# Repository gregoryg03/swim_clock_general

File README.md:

# swim_clock_general
General Project code development and other related files

Basic testing is being conducted on Arduino Uno with 4 7-segment LEDs

Plan to move to ESP 32

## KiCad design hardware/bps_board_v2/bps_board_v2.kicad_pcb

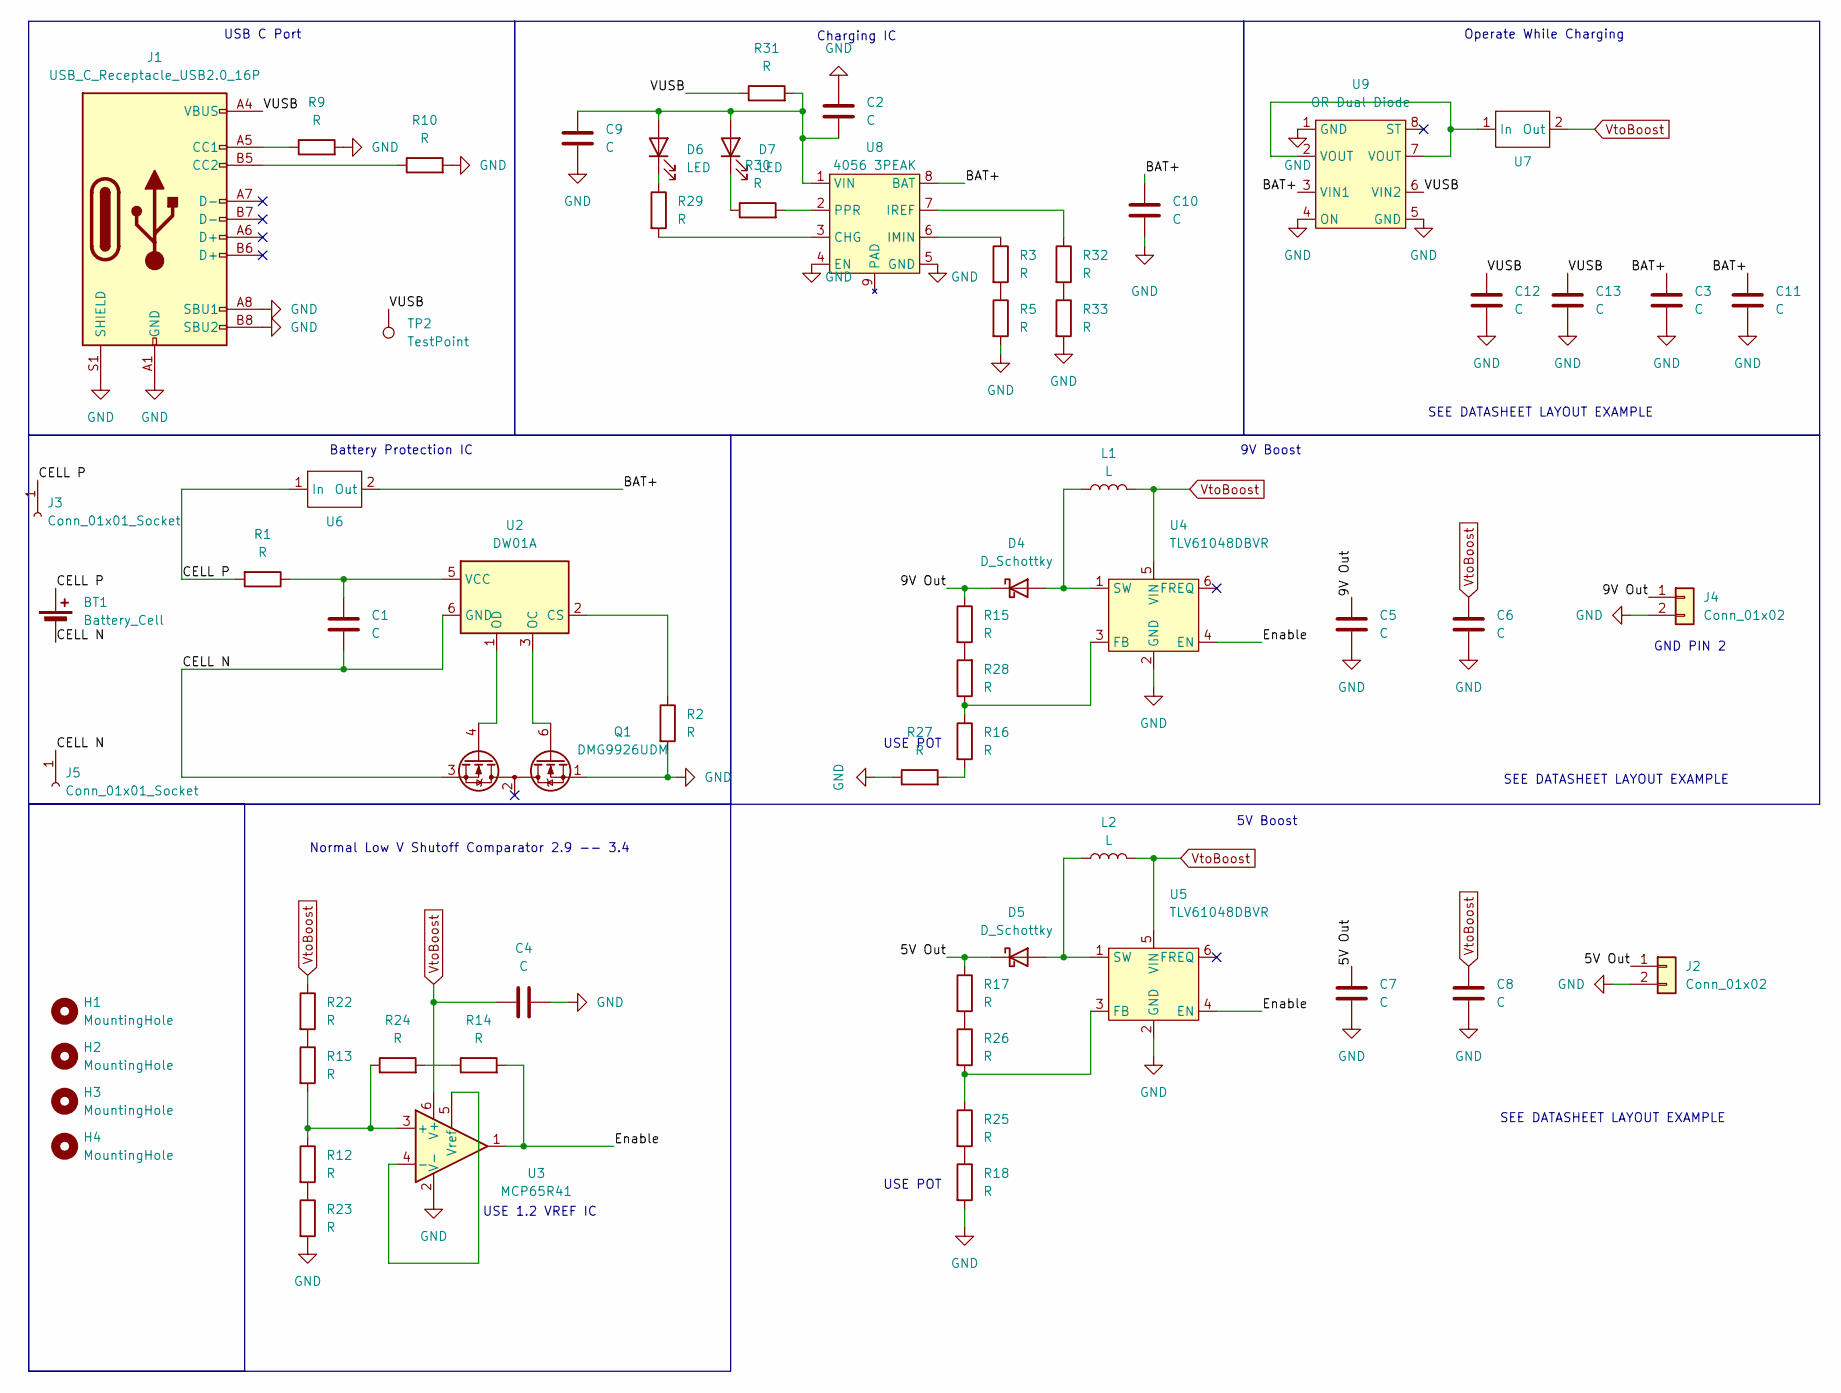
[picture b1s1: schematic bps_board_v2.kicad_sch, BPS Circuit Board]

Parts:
BT1: Battery_Cell; 18650 8mm Strip
C1, C2, C3, C4, C5, C6, C7, C8, C9, C10, C11, C12, C13: C; C_1206_3216Metric_Pad1.33x1.80mm_HandSolder
D4, D5: D_Schottky; MBRS130LT3G Diode
D6, D7: LED; LED_0603_1608Metric_Pad1.05x0.95mm_HandSolder
H1, H2, H3, H4: MountingHole; MountingHole_3.2mm_M3
J1: USB_C_Receptacle_USB2.0_16P; USB_C_Receptacle_GCT_USB4085
J2, J4: Conn_01x02; JST_EH_B2B-EH-A_1x02_P2.50mm_Vertical
J3, J5: Conn_01x01_Socket; EmptyPad
L1, L2: L; InductorFixed
Q1: DMG9926UDM; SOT-23-6
R1, R2, R3, R5, R9, R10, R12, R13, R14, R15, R16, R17, R18, R22, R23, R24, R25, R26, R27, R28, R29, R30, R31, R32, R33: R; R_1206_3216Metric_Pad1.30x1.75mm_HandSolder
TP2: TestPoint; TestPoint_THTPad_2.5x2.5mm_Drill1.2mm
U2: DW01A; SOT-23-6
U3: MCP65R41; SOT-23-6
U4, U5: TLV61048DBVR; SOT-23-6_Handsoldering
U6, U7: 22AWG Wire Jump
U8: 4056 3PEAK; SOIC-8-1EP_3.9x4.9mm_P1.27mm_EP2.41x3.3mm_ThermalVias
U9: OR Dual Diode; SOT-583-8

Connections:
/5V Out: C7.1, D5.1 (K), J2.1, R17.1
/9V Out: C5.1, D4.1 (K), J4.1, R15.1
/BAT+: C3.1, C10.1, C11.1, U6.2 (Out), U8.8 (BAT), U9.3 (VIN1)
/CELL N: BT1.2 (-), C1.2, J5.1, Q1.3 (S2), U2.6 (GND)
/CELL P: BT1.1 (+), J3.1, R1.2, U6.1 (In)
/Enable: R14.2, U3.1, U4.4 (EN), U5.4 (EN)
/VUSB: C12.1, C13.1, J1.A4 (VBUS), J1.A9 (VBUS), J1.B4 (VBUS), J1.B9 (VBUS), R31.1, TP2.1, U9.6 (VIN2)
GND: C2.1, C3.2, C4.2, C5.2, C6.2, C7.2, C8.2, C9.2, C10.2, C11.2, C12.2, C13.2, J1.A1 (GND), J1.A8 (SBU1), J1.A12 (GND), J1.B1 (GND), J1.B8 (SBU2), J1.B12 (GND), J1.S1 (SHIELD), J2.2, J4.2, Q1.1 (D1), R2.2, R5.2, R9.2, R10.2, R18.2, R23.2, R27.1, R33.2, U3.2 (V-), U4.2 (GND), U5.2 (GND), U8.4 (EN), U8.5 (GND), U9.1 (GND), U9.4 (ON), U9.5 (GND)
unnamed: D4.2 (A), L1.1, U4.1 (SW)
unnamed: D5.2 (A), L2.1, U5.1 (SW)
unnamed: C2.2, C9.1, D6.2 (A), D7.2 (A), R31.2, U8.1 (VIN)
unnamed: D6.1 (K), R29.1
unnamed: D7.1 (K), R30.1
unnamed: J1.A5 (CC1), R9.1
unnamed: J1.B5 (CC2), R10.1
unnamed: Q1.6 (G1), U2.3 (OC)
unnamed: Q1.4 (G2), U2.1 (OD)
unnamed: R3.2, R5.1
unnamed: R12.2, R23.1
unnamed: R13.1, R22.2
unnamed: R14.1, R24.2
unnamed: R15.2, R28.2
unnamed: R16.2, R27.2
unnamed: R17.2, R26.1
unnamed: R18.1, R25.2
unnamed: R32.2, R33.1
unnamed: R2.1, U2.2 (CS)
unnamed: C1.1, R1.1, U2.5 (VCC)
unnamed: R12.1, R13.2, R24.1, U3.3 (+)
unnamed: U3.4 (-), U3.5 (Vref)
unnamed: R16.1, R28.1, U4.3 (FB)
unnamed: R25.1, R26.2, U5.3 (FB)
unnamed: U7.1 (In), U9.2 (VOUT), U9.7 (VOUT)
unnamed: R29.2, U8.3 (CHG)
unnamed: R3.1, U8.6 (IMIN)
unnamed: R32.1, U8.7 (IREF)
unnamed: R30.2, U8.2 (PPR)
VtoBoost: C4.1, C6.1, C8.1, L1.2, L2.2, R22.1, U3.6 (V+), U4.5 (VIN), U5.5 (VIN), U7.2 (Out)

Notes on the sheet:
USE 1.2 VREF IC
SEE DATASHEET LAYOUT EXAMPLE
Battery Protection IC
Charging IC
GND PIN 2
USE POT
5V Boost
Operate While Charging
USB C Port
Normal Low V Shutoff Comparator 2.9 -- 3.4
9V Boost

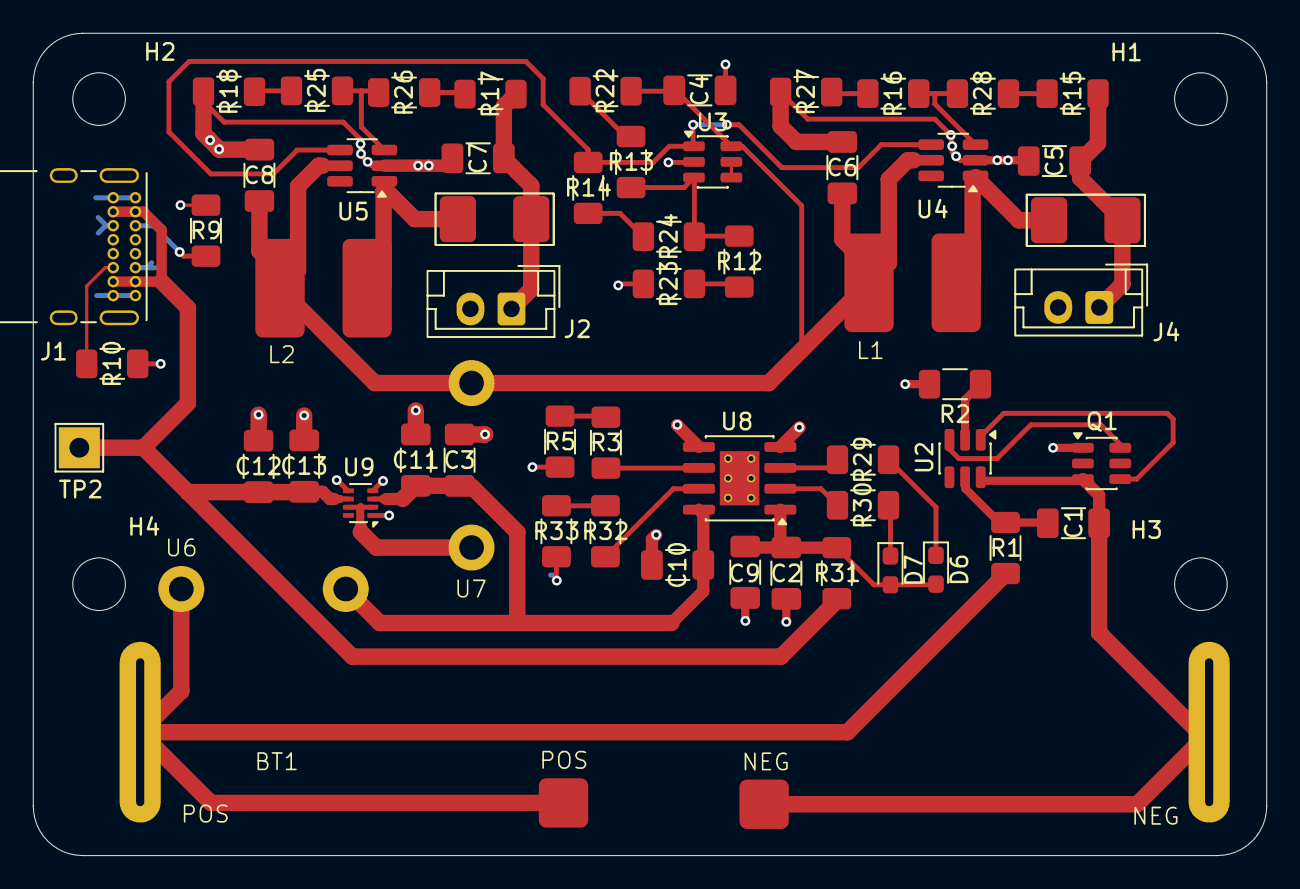
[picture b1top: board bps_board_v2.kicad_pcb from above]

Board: 2 copper layers, 75.0 x 50.0 mm, 64 parts (0 on the bottom side), 38 nets.

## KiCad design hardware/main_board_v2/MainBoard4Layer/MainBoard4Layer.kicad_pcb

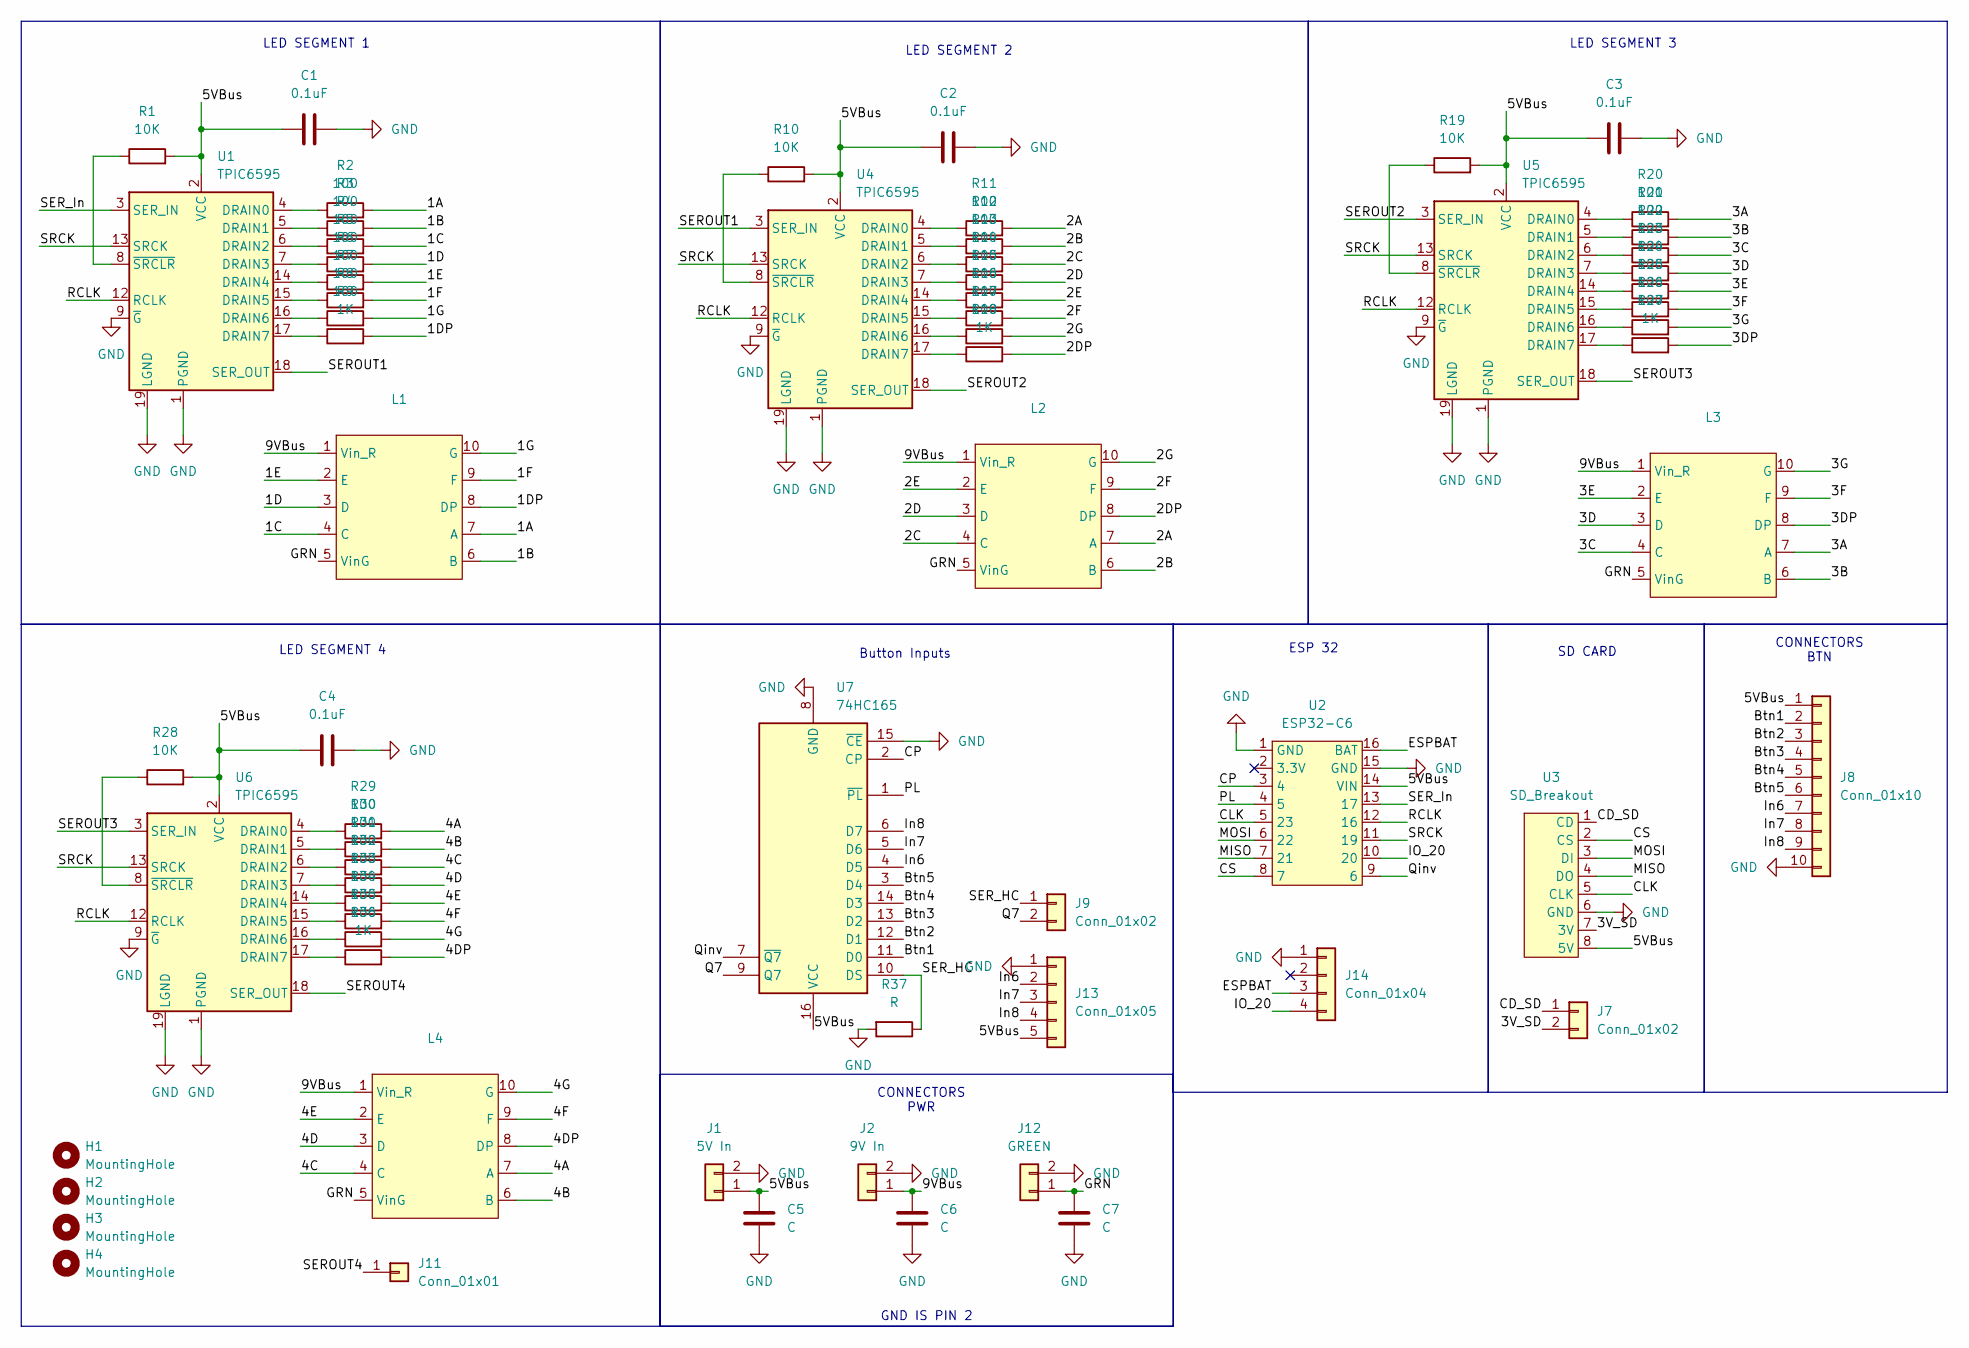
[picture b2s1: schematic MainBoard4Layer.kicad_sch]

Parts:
C1, C2, C3, C4: 0.1uF; C_1206_3216Metric_Pad1.33x1.80mm_HandSolder
C5, C6, C7: C; C_1206_3216Metric_Pad1.33x1.80mm_HandSolder
H1, H2, H3, H4: MountingHole; MountingHole_3.2mm_M3
J1: 5V In; JST_EH_B2B-EH-A_1x02_P2.50mm_Vertical
J2: 9V In; JST_EH_B2B-EH-A_1x02_P2.50mm_Vertical
J7, J9: Conn_01x02; PinHeader_1x02_P2.54mm_Vertical
J8: Conn_01x10; MOLEX_10_PIN
J11: Conn_01x01; PinSocket_1x01_P2.54mm_Vertical
J12: GREEN; JST_EH_B2B-EH-A_1x02_P2.50mm_Vertical
J13: Conn_01x05; PinHeader_1x05_P2.54mm_Vertical
J14: Conn_01x04; PinHeader_1x04_P2.54mm_Vertical
L1, L2, L3, L4: 7SEG_LED_2.3IN
R1, R10, R19, R28: 10K; R_1206_3216Metric_Pad1.30x1.75mm_HandSolder
R2, R3, R4, R5, R6, R7, R8, R11, R12, R13, R14, R15, R16, R17, R20, R21, R22, R23, R24, R25, R26, R29, R30, R31, R32, R33, R34, R35: 100; R_1206_3216Metric_Pad1.30x1.75mm_HandSolder
R9, R18, R27, R36: 1K; R_1206_3216Metric_Pad1.30x1.75mm_HandSolder
R37: R; R_1206_3216Metric_Pad1.30x1.75mm_HandSolder
U1, U4, U5, U6: TPIC6595; DIP-20_W7.62mm_Socket
U2: ESP32-C6; ESPC6_BEETLE
U3: SD_Breakout; SD Card
U7: 74HC165; DIP-16_W7.62mm_Socket

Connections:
/1A: L1.7 (A), R2.2
/1B: L1.6 (B), R3.2
/1C: L1.4 (C), R4.2
/1D: L1.3 (D), R5.2
/1DP: L1.8 (DP), R9.2
/1E: L1.2 (E), R6.2
/1F: L1.9 (F), R7.2
/1G: L1.10 (G), R8.2
/2A: L2.7 (A), R11.2
/2B: L2.6 (B), R12.2
/2C: L2.4 (C), R13.2
/2D: L2.3 (D), R14.2
/2DP: L2.8 (DP), R18.2
/2E: L2.2 (E), R15.2
/2F: L2.9 (F), R16.2
/2G: L2.10 (G), R17.2
/3A: L3.7 (A), R20.2
/3B: L3.6 (B), R21.2
/3C: L3.4 (C), R22.2
/3D: L3.3 (D), R23.2
/3DP: L3.8 (DP), R27.2
/3E: L3.2 (E), R24.2
/3F: L3.9 (F), R25.2
/3G: L3.10 (G), R26.2
/3V_SD: J7.2, U3.7 (3V)
/4A: L4.7 (A), R29.2
/4B: L4.6 (B), R30.2
/4C: L4.4 (C), R31.2
/4D: L4.3 (D), R32.2
/4DP: L4.8 (DP), R36.2
/4E: L4.2 (E), R33.2
/4F: L4.9 (F), R34.2
/4G: L4.10 (G), R35.2
/5VBus: C1.1, C2.1, C3.1, C4.1, C5.1, J1.1, J8.1, J13.5, R1.2, R10.2, R19.2, R28.2, U1.2 (VCC), U2.14 (VIN), U3.8 (5V), U4.2 (VCC), U5.2 (VCC), U6.2 (VCC), U7.16 (VCC)
/9VBus: C6.1, J2.1, L1.1 (Vin_R), L2.1 (Vin_R), L3.1 (Vin_R), L4.1 (Vin_R)
/Btn1: J8.2, U7.11 (D0)
/Btn2: J8.3, U7.12 (D1)
/Btn3: J8.4, U7.13 (D2)
/Btn4: J8.5, U7.14 (D3)
/Btn5: J8.6, U7.3 (D4)
/CD_SD: J7.1, U3.1 (CD)
/CLK: U2.5 (23), U3.5 (CLK)
/CP: U2.3 (4), U7.2 (CP)
/CS: U2.8 (7), U3.2 (CS)
/ESPBAT: J14.3, U2.16 (BAT)
/GRN: C7.1, J12.1, L1.5 (VinG), L2.5 (VinG), L3.5 (VinG), L4.5 (VinG)
/IO_20: J14.4, U2.10 (20)
/In6: J8.7, J13.2, U7.4 (D5)
/In7: J8.8, J13.3, U7.5 (D6)
/In8: J8.9, J13.4, U7.6 (D7)
/MISO: U2.7 (21), U3.4 (DO)
/MOSI: U2.6 (22), U3.3 (DI)
/PL: U2.4 (5), U7.1 (~PL)
/Q7: J9.2, U7.9 (Q7)
/Qinv: U2.9 (6), U7.7 (~Q7)
/RCLK: U1.12 (RCLK), U2.12 (16), U4.12 (RCLK), U5.12 (RCLK), U6.12 (RCLK)
/SEROUT1: U1.18 (SER_OUT), U4.3 (SER_IN)
/SEROUT2: U4.18 (SER_OUT), U5.3 (SER_IN)
/SEROUT3: U5.18 (SER_OUT), U6.3 (SER_IN)
/SEROUT4: J11.1, U6.18 (SER_OUT)
/SER_HC: J9.1, R37.1, U7.10 (DS)
/SER_In: U1.3 (SER_IN), U2.13 (17)
/SRCK: U1.13 (SRCK), U2.11 (19), U4.13 (SRCK), U5.13 (SRCK), U6.13 (SRCK)
GND: C1.2, C2.2, C3.2, C4.2, C5.2, C6.2, C7.2, J1.2, J2.2, J8.10, J12.2, J13.1, J14.1, R37.2, U1.1 (PGND), U1.9 (~G), U1.10 (PGND), U1.11 (PGND), U1.19 (LGND), U1.20 (PGND), U2.1 (GND), U2.15 (GND), U3.6 (GND), U4.1 (PGND), U4.9 (~G), U4.10 (PGND), U4.11 (PGND), U4.19 (LGND), U4.20 (PGND), U5.1 (PGND), U5.9 (~G), U5.10 (PGND), U5.11 (PGND), U5.19 (LGND), U5.20 (PGND), U6.1 (PGND), U6.9 (~G), U6.10 (PGND), U6.11 (PGND), U6.19 (LGND), U6.20 (PGND), U7.8 (GND), U7.15 (~CE)
unnamed: R2.1, U1.4 (DRAIN0)
unnamed: R3.1, U1.5 (DRAIN1)
unnamed: R4.1, U1.6 (DRAIN2)
unnamed: R5.1, U1.7 (DRAIN3)
unnamed: R6.1, U1.14 (DRAIN4)
unnamed: R7.1, U1.15 (DRAIN5)
unnamed: R8.1, U1.16 (DRAIN6)
unnamed: R9.1, U1.17 (DRAIN7)
unnamed: R1.1, U1.8 (~SRCLR)
unnamed: R11.1, U4.4 (DRAIN0)
unnamed: R12.1, U4.5 (DRAIN1)
unnamed: R13.1, U4.6 (DRAIN2)
unnamed: R14.1, U4.7 (DRAIN3)
unnamed: R15.1, U4.14 (DRAIN4)
unnamed: R16.1, U4.15 (DRAIN5)
unnamed: R17.1, U4.16 (DRAIN6)
unnamed: R18.1, U4.17 (DRAIN7)
unnamed: R10.1, U4.8 (~SRCLR)
unnamed: R20.1, U5.4 (DRAIN0)
unnamed: R21.1, U5.5 (DRAIN1)
unnamed: R22.1, U5.6 (DRAIN2)
unnamed: R23.1, U5.7 (DRAIN3)
unnamed: R24.1, U5.14 (DRAIN4)
unnamed: R25.1, U5.15 (DRAIN5)
unnamed: R26.1, U5.16 (DRAIN6)
unnamed: R27.1, U5.17 (DRAIN7)
unnamed: R19.1, U5.8 (~SRCLR)
unnamed: R29.1, U6.4 (DRAIN0)
unnamed: R30.1, U6.5 (DRAIN1)
unnamed: R31.1, U6.6 (DRAIN2)
unnamed: R32.1, U6.7 (DRAIN3)
unnamed: R33.1, U6.14 (DRAIN4)
unnamed: R34.1, U6.15 (DRAIN5)
unnamed: R35.1, U6.16 (DRAIN6)
unnamed: R36.1, U6.17 (DRAIN7)
unnamed: R28.1, U6.8 (~SRCLR)

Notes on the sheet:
LED SEGMENT 2
Button Inputs
LED SEGMENT 4
SD CARD
CONNECTORS BTN
ESP 32
LED SEGMENT 3
GND IS PIN 2
LED SEGMENT 1
CONNECTORS PWR

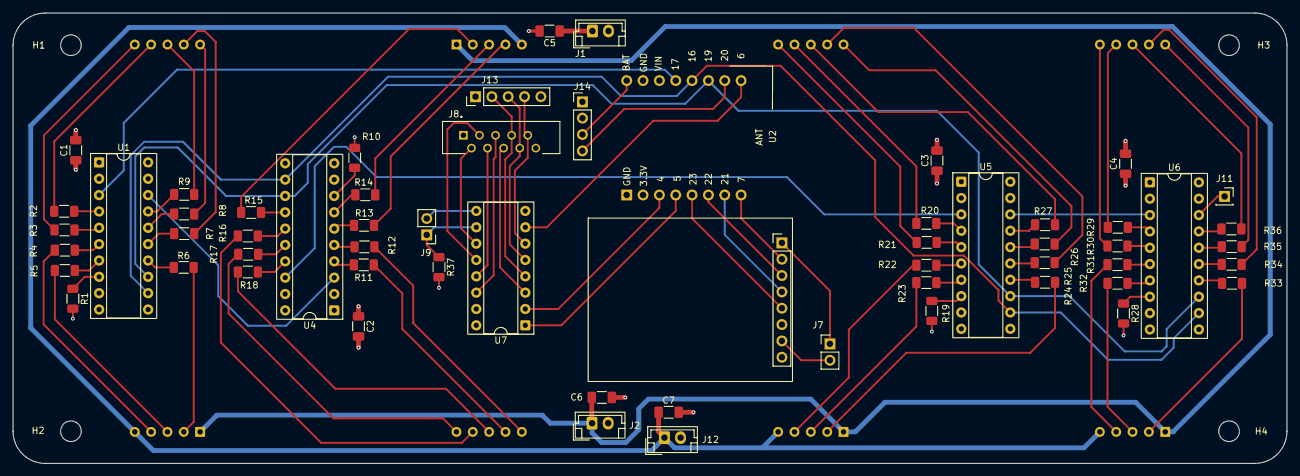
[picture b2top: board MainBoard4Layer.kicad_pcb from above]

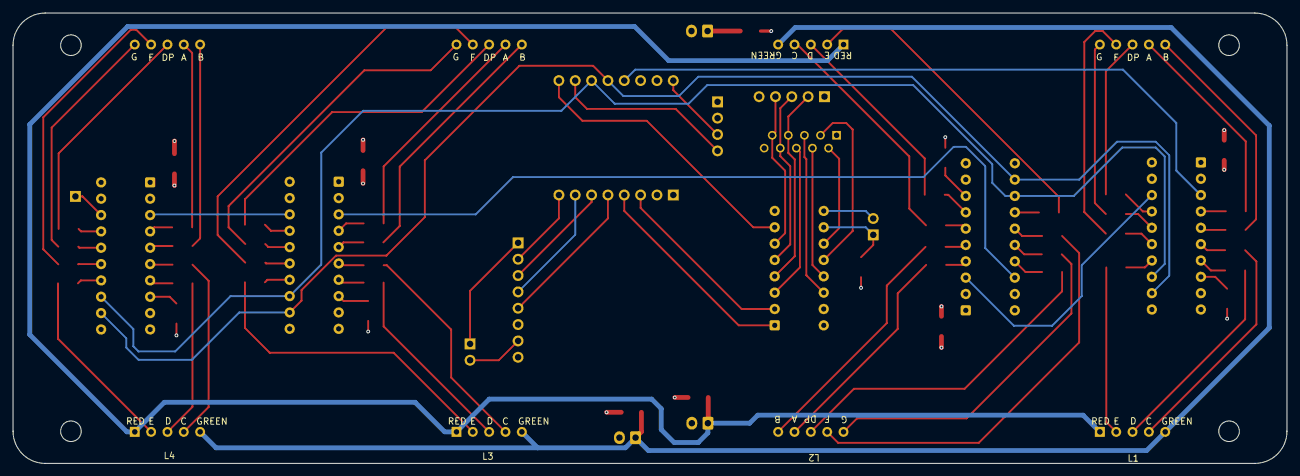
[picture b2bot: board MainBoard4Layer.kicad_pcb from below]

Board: 4 copper layers, 198.0 x 70.0 mm, 68 parts (4 on the bottom side), 100 nets.

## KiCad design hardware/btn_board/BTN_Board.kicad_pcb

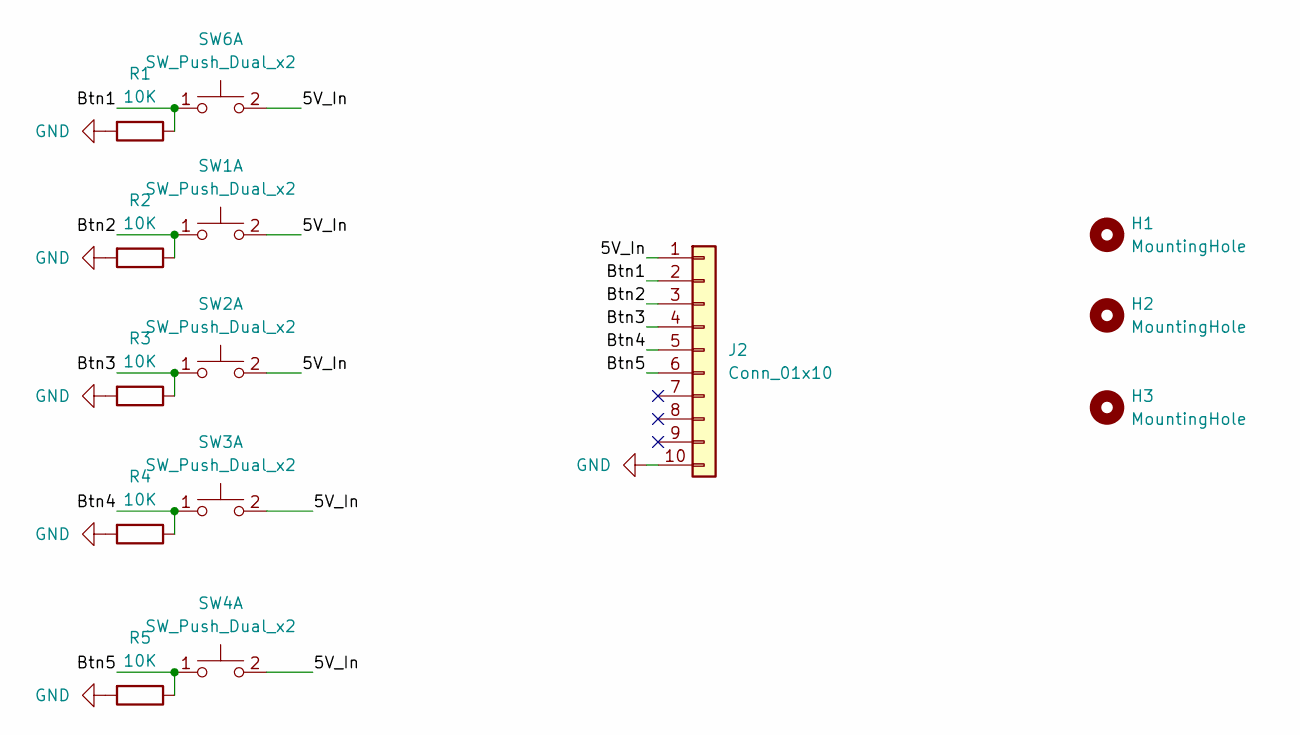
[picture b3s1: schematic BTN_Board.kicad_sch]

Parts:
H1, H2, H3: MountingHole; MountingHole_3.2mm_M3
J2: Conn_01x10; MOLEX_10_PIN
R1, R2, R3, R4, R5: 10K; R_1206_3216Metric_Pad1.30x1.75mm_HandSolder
SW1, SW2, SW3, SW4, SW6: SW_Push_Dual_x2; 12mm BTN Backside

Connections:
/5V_In: J2.1, SW1.2 (D), SW2.2 (D), SW3.2 (D), SW4.2 (D), SW6.2 (D); also elsewhere on the board
/Btn1: J2.2, R1.1, SW6.1 (C); also elsewhere on the board
/Btn2: J2.3, R2.1, SW1.1 (C)
/Btn3: J2.4, R3.1, SW2.1 (C)
/Btn4: J2.5, R4.1, SW3.1 (C)
/Btn5: J2.6, R5.1, SW4.1 (C)
GND: J2.10, R1.2, R2.2, R3.2, R4.2, R5.2

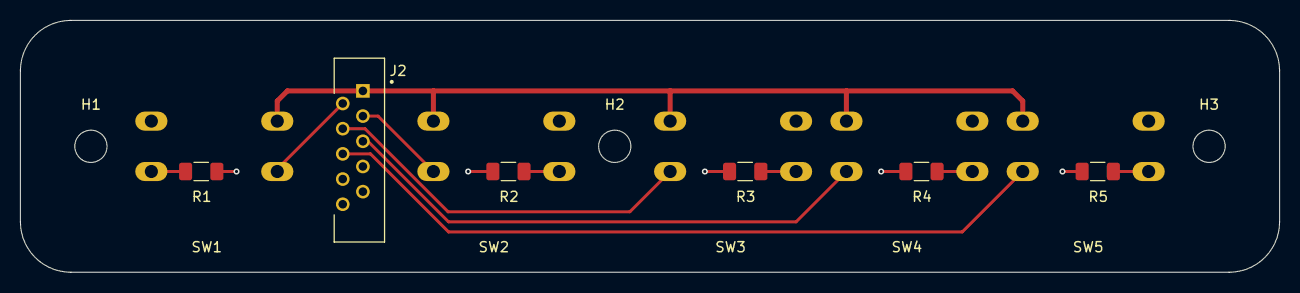
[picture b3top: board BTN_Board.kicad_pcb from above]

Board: 2 copper layers, 125.0 x 25.0 mm, 14 parts (0 on the bottom side), 7 nets.

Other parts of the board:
SW5: SW_Push_Dual_x2; 12mm BTN Backside

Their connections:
/5V_In: SW5.2 (D); also elsewhere on the board
/Btn1: SW5.1 (C); also elsewhere on the board

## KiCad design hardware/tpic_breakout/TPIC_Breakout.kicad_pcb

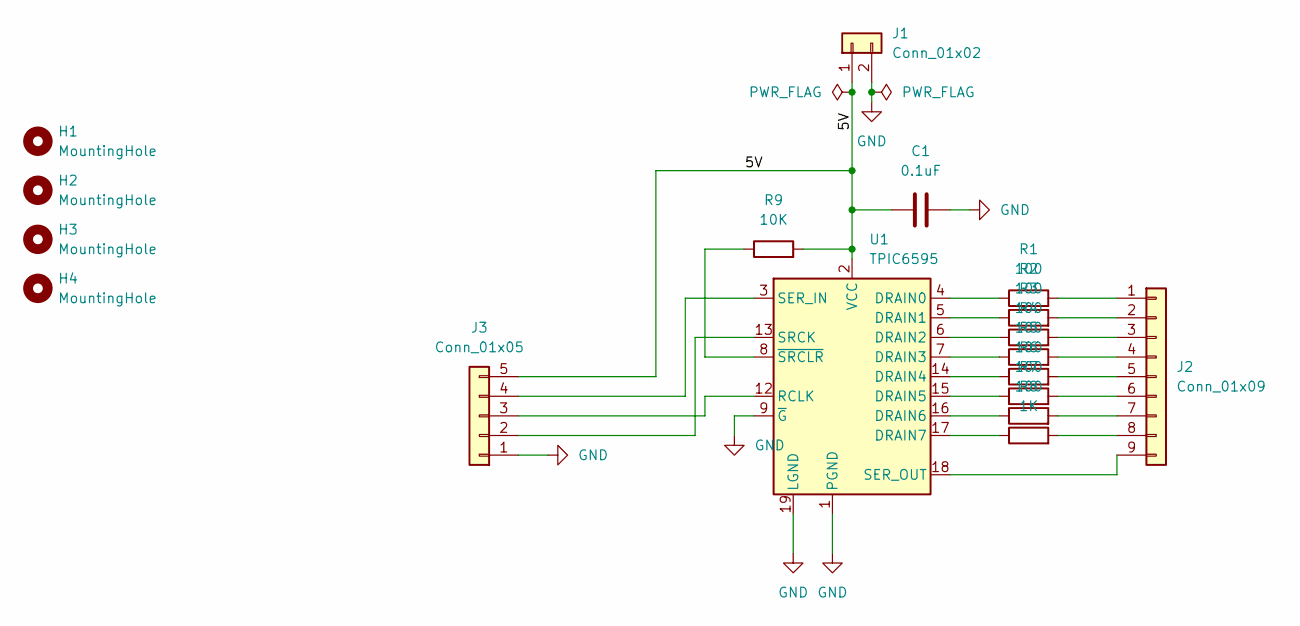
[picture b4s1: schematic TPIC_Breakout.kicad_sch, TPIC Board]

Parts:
C1: 0.1uF; C_Disc_D5.0mm_W2.5mm_P2.50mm
H1, H2, H3, H4: MountingHole; MountingHole_2.2mm_M2
J1: Conn_01x02; JST_EH_B2B-EH-A_1x02_P2.50mm_Vertical
J2: Conn_01x09; PinSocket_1x09_P2.54mm_Vertical
J3: Conn_01x05; PinSocket_1x05_P2.54mm_Vertical
R1, R2, R3, R4, R5, R6, R7: 100; R_1206_3216Metric_Pad1.30x1.75mm_HandSolder
R8: 1K; R_1206_3216Metric_Pad1.30x1.75mm_HandSolder
R9: 10K; R_1206_3216Metric_Pad1.30x1.75mm_HandSolder
U1: TPIC6595; DIP-20_W7.62mm

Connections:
/5V: C1.1, J1.1, J3.5, R9.2, U1.2 (VCC)
GND: C1.2, J1.2, J3.1, U1.1 (PGND), U1.9 (~G), U1.10 (PGND), U1.11 (PGND), U1.19 (LGND), U1.20 (PGND)
unnamed: J2.1, R1.2
unnamed: J2.2, R2.2
unnamed: J2.3, R3.2
unnamed: J2.4, R4.2
unnamed: J2.5, R5.2
unnamed: J2.6, R6.2
unnamed: J2.7, R7.2
unnamed: J2.8, R8.2
unnamed: J2.9, U1.18 (SER_OUT)
unnamed: J3.2, U1.13 (SRCK)
unnamed: J3.3, U1.12 (RCLK)
unnamed: J3.4, U1.3 (SER_IN)
unnamed: R1.1, U1.4 (DRAIN0)
unnamed: R2.1, U1.5 (DRAIN1)
unnamed: R3.1, U1.6 (DRAIN2)
unnamed: R4.1, U1.7 (DRAIN3)
unnamed: R5.1, U1.14 (DRAIN4)
unnamed: R6.1, U1.15 (DRAIN5)
unnamed: R7.1, U1.16 (DRAIN6)
unnamed: R8.1, U1.17 (DRAIN7)
unnamed: R9.1, U1.8 (~SRCLR)

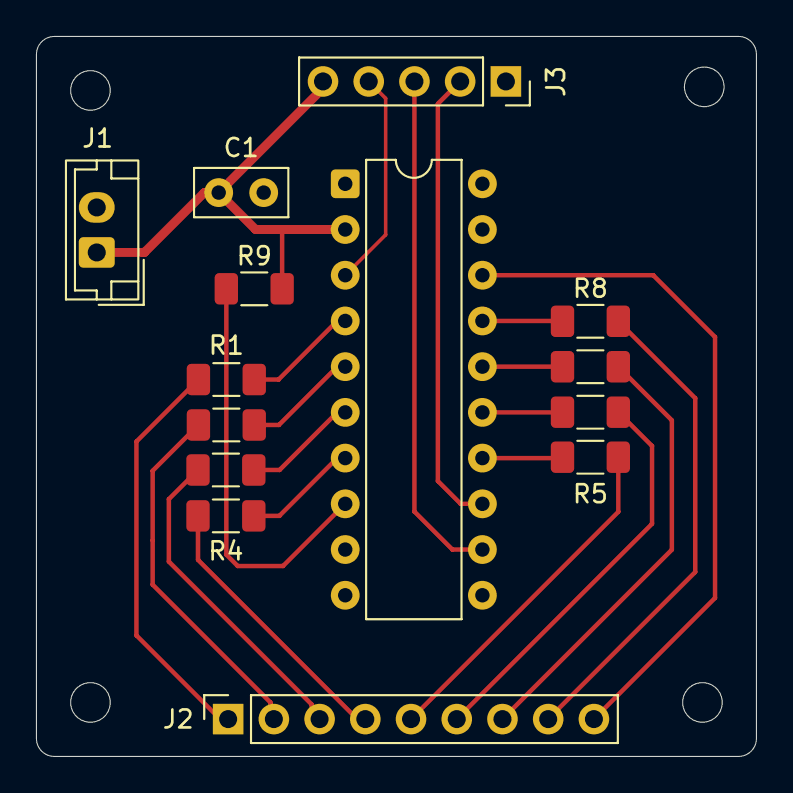
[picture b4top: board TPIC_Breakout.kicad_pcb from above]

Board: 2 copper layers, 40.0 x 40.0 mm, 18 parts (0 on the bottom side), 23 nets.

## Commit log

2026-02-19 Add main.ino and updated README.md
2026-02-19 Updated main.ino to the correct file
2026-02-19 Organized project to include hardware folder
2026-02-19 Added empty hardware folder
2026-02-19 Created hardware sub-folders to add kicad files from PC
2026-02-19 Added files from KICAD
2026-02-20 Updated main_boad sch | Created btn_board files
2026-02-20 Changed dp check to bitwise | adding setting LED blank before 0s | Shortent 0s in setup | Formatting
2026-02-27 Migrated from Arduino IDE to Platform.io project is VSCode
2026-03-01 created button testing project and updated main in vscode project to count down
2026-03-01 Updated button logic and added options for loading order from shiftreg | moved timer reset location in cscode_prj
2026-03-01 Initial edits for adding debounce
2026-03-01 Fixed case break and removed extra input
2026-03-02 added debounce to the button_testing | Integrated this work into vscode_project and rearchitectured the files
2026-03-02 added pause functionallity
2026-03-05 Updated main board to finish footprint assignment
2026-03-05 Added custom footprints in pretty folder
2026-03-05 began adding classes for state monitor
2026-03-08 continued adding the features for different modes of operation
2026-03-08 Draft of btn board
2026-03-08 Finished btn board and generated gerbers
2026-03-09 Started PCB layout for mainboard
2026-03-09 Added the states and removed all errors to prepare for test. Added array items for mode select
2026-03-10 Edits and troubleshooting
2026-03-10 Debugging, pause button sucessfully works with the states rework
2026-03-11 Added mode selection, errors with switching modes to fix
2026-03-12 Replaced switch case with a function table for mode selection and simplified the mode switching heler function
2026-03-13 began adding SD card functionality
2026-03-13 typo
2026-03-15 Began implementing the program mode to write to the SD card
2026-03-16 Started 2 layer mainboard, switching to 4 layer
2026-03-16 Completed the 4 layer main board version, ready to review
2026-03-20 Troubleshooting SD card. Addded function table, fixed reading, added a mode for shutdown
2026-03-22 Refactored SD cpp and h file. Ready to incorporate into other files
2026-03-22 Updated SD action calls, ready to implement reading back from file
2026-03-24 Added SD.cpp calls and tested sucessful implementation of file read/write for program and countdown modes
2026-03-25 Added blinking to program mode data entry for selected digit, need to fix timing on mode entry
2026-03-26 Fixed blinking in prg mode, reworked the pause logic, introduced error with switching out of program mode, need to define desired behavior
2026-04-04 Merged firmware folder from latest branch to main
2026-04-06 Added action cycle to cycle modes which fixed bug preventing program mode from exiting smoothly
2026-04-06 Fixd bug in program mode that allowed multiple digits to blink after setting the selected interval
2026-04-06 Changed starting action to be paused, press btn 1 to start count up
2026-04-16 Created project for ESP 32, SD card tested and ready to transfer code
2026-04-23 Created a version 2 for the bps board to incorporate the improvements, added the symobls and footprint
2026-04-24 Started adding the code to esp project
2026-04-30 Routing bps_board_v2
2026-04-30 Routing work on bps_board_v2
2026-05-01 Completed bps_v2
2026-05-04 Working on esp buttons
2026-05-05 Fixed CMake issue, contined writing the buttons.c file
2026-05-06 continued working on buttons.c. Added events folder
2026-05-07 Finshed buttons, working through errors, set up test in main
2026-05-08 Tested on ESP, troubleshooting reset
2026-05-11 troubleshooting buttons
2026-05-15 Troubleshooting buttons, found issue with the edge_detect
2026-05-16 Buttons work
2026-05-16 Started display
2026-05-16 Display works, init complete
2026-05-17 Migrating events and display
2026-05-19 Added sd items to test via fixed array
2026-05-21 worked on events and display
2026-05-22 Continued display and events
2026-05-25 Updates to event and display, began testing
2026-05-26 Display working! Up and Down modes are functional
2026-05-27 pg mode functional, fixed issues with display and state machine
2026-05-27 Started sd integration
2026-05-28 fixed sd errors, made c file
2026-05-29 Sucessfully tested SD card
2026-05-30 Added sd functions
2026-06-01 added sd items to events, troubleshooting issue
2026-06-15 began sd testing/integration
2026-06-30 Fixed SD card, changed to not use test array
